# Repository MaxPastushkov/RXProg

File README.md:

RXProg uses an STM32 to emulate the drum machine's SRAM chips, allowing programming over USB

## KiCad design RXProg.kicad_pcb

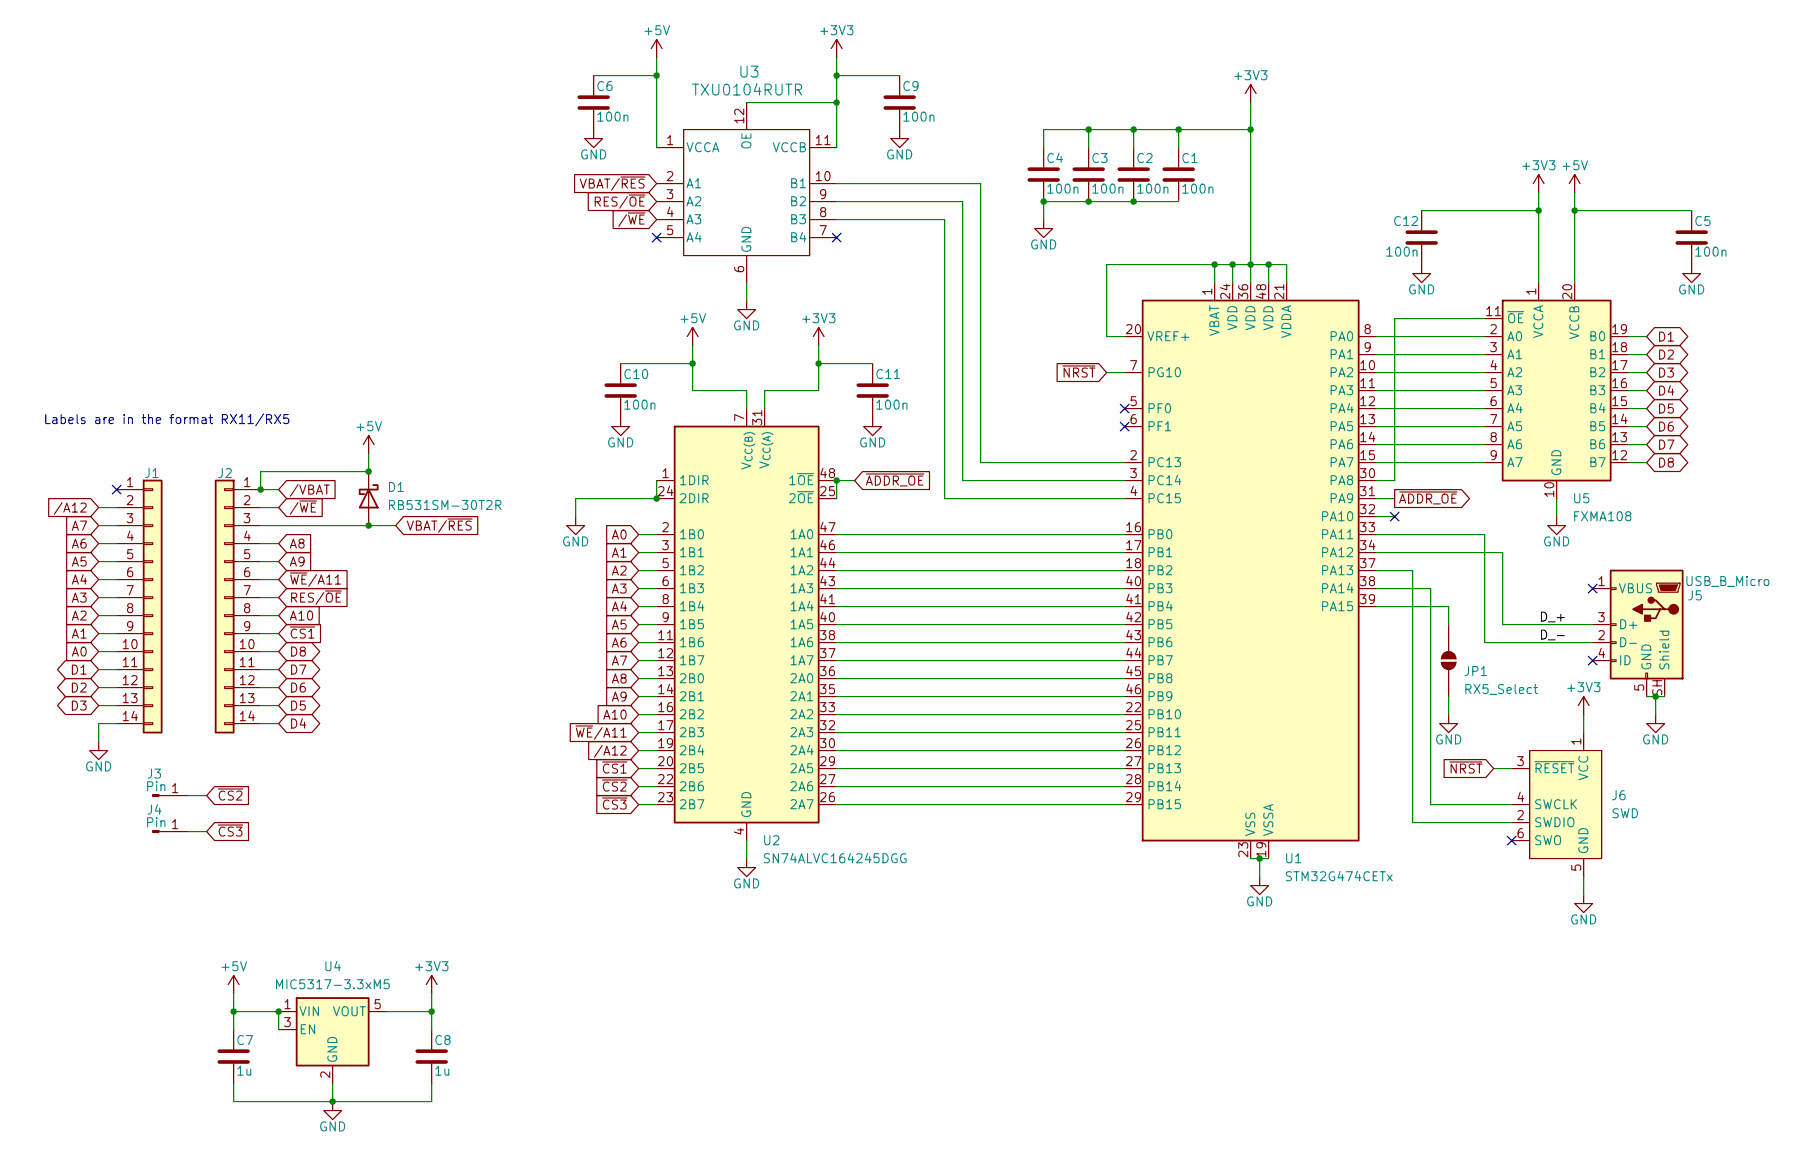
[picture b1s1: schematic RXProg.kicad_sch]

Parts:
C1, C2, C3, C4, C5, C6, C9, C10, C11, C12: 100n; C_0201_0603Metric
C7, C8: 1u; C_0201_0603Metric
D1: RB531SM-30T2R; D_SOD-523
J1, J2: Conn_01x14; PinHeader_1x14_P2.54mm_Vertical
J3, J4: Pin
J5: USB_B_Micro; USB_Micro-B_Amphenol_10103594-0001LF_Horizontal
J6: SWD; Tag-Connect_TC2030-IDC-NL_2x03_P1.27mm_Vertical
JP1: RX5_Select; SolderJumper-2_P1.3mm_Open_RoundedPad1.0x1.5mm
U1: STM32G474CETx; LQFP-48_7x7mm_P0.5mm
U2: SN74ALVC164245DGG; TSSOP-48_6.1x12.5mm_P0.5mm
U3: TXU0104RUTR; QFN_04RUTR_TEX
U4: MIC5317-3.3xM5; SOT-23-5
U5: FXMA108; WQFN-20-1EP_2.5x4.5mm_P0.5mm_EP1x2.9mm

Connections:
+3V3: C1.1, C2.1, C3.1, C4.1, C8.1, C9.1, C11.1, C12.1, J6.1 (VCC), U1.1 (VBAT), U1.20 (VREF+), U1.21 (VDDA), U1.24 (VDD), U1.36 (VDD), U1.48 (VDD), U2.31 (V_{CC(A)}), U2.42 (V_{CC(A)}), U3.11 (VCCB), U3.12 (OE), U4.5 (VOUT), U5.1 (VCCA)
/D_+: J5.3 (D+), U1.34 (PA12)
/D_-: J5.2 (D-), U1.33 (PA11)
A0: J1.10, U2.2 (1B0)
A1: J1.9, U2.3 (1B1)
A2: J1.8, U2.5 (1B2)
A3: J1.7, U2.6 (1B3)
A4: J1.6, U2.8 (1B4)
A5: J1.5, U2.9 (1B5)
A6: J1.4, U2.11 (1B6)
A7: J1.3, U2.12 (1B7)
A8: J2.4, U2.13 (2B0)
A9: J2.5, U2.14 (2B1)
A10: J2.8, U2.16 (2B2)
D1: J1.11, U5.19 (B0)
D2: J1.12, U5.18 (B1)
D3: J1.13, U5.17 (B2)
D4: J2.14, U5.16 (B3)
D5: J2.13, U5.15 (B4)
D6: J2.12, U5.14 (B5)
D7: J2.11, U5.13 (B6)
D8: J2.10, U5.12 (B7)
GND: C1.2, C2.2, C3.2, C4.2, C5.2, C6.2, C7.2, C8.2, C9.2, C10.2, C11.2, C12.2, J1.14, J5.5 (GND), J5.SH (Shield), J6.5 (GND), JP1.1 (A), U1.19 (VSSA), U1.23 (VSS), U1.35 (VSS), U1.47 (VSS), U2.1 (1DIR), U2.4 (GND), U2.10 (GND), U2.15 (GND), U2.21 (GND), U2.24 (2DIR), U2.28 (GND), U2.34 (GND), U2.39 (GND), U2.45 (GND), U3.6 (GND), U4.2 (GND), U5.10 (GND)
unnamed: J6.4 (SWCLK), U1.38 (PA14)
unnamed: J6.2 (SWDIO), U1.37 (PA13)
unnamed: JP1.2 (B), U1.39 (PA15)
unnamed: U1.8 (PA0), U5.2 (A0)
unnamed: U1.9 (PA1), U5.3 (A1)
unnamed: U1.10 (PA2), U5.4 (A2)
unnamed: U1.11 (PA3), U5.5 (A3)
unnamed: U1.12 (PA4), U5.6 (A4)
unnamed: U1.13 (PA5), U5.7 (A5)
unnamed: U1.14 (PA6), U5.8 (A6)
unnamed: U1.15 (PA7), U5.9 (A7)
unnamed: U1.30 (PA8), U5.11 (~OE)
unnamed: U1.16 (PB0), U2.47 (1A0)
unnamed: U1.17 (PB1), U2.46 (1A1)
unnamed: U1.18 (PB2), U2.44 (1A2)
unnamed: U1.40 (PB3), U2.43 (1A3)
unnamed: U1.41 (PB4), U2.41 (1A4)
unnamed: U1.42 (PB5), U2.40 (1A5)
unnamed: U1.43 (PB6), U2.38 (1A6)
unnamed: U1.44 (PB7), U2.37 (1A7)
unnamed: U1.45 (PB8), U2.36 (2A0)
unnamed: U1.46 (PB9), U2.35 (2A1)
unnamed: U1.22 (PB10), U2.33 (2A2)
unnamed: U1.25 (PB11), U2.32 (2A3)
unnamed: U1.26 (PB12), U2.30 (2A4)
unnamed: U1.27 (PB13), U2.29 (2A5)
unnamed: U1.28 (PB14), U2.27 (2A6)
unnamed: U1.29 (PB15), U2.26 (2A7)
unnamed: U1.2 (PC13), U3.10 (B1)
unnamed: U1.3 (PC14), U3.9 (B2)
unnamed: U1.4 (PC15), U3.8 (B3)
RES/~OE: J2.7, U3.3 (A2)
VBAT/~RES: D1.2 (A), J2.3, U3.2 (A1)
/A12: J1.2, U2.19 (2B4)
/VBAT: C5.1, C6.1, C7.1, C10.1, D1.1 (K), J2.1, U2.7 (V_{CC(B)}), U2.18 (V_{CC(B)}), U3.1 (VCCA), U4.1 (VIN), U4.3 (EN), U5.20 (VCCB)
/~WE: J2.2, U3.4 (A3)
~ADDR_OE: U1.31 (PA9), U2.25 (2~OE), U2.48 (1~OE)
~CS1: J2.9, U2.20 (2B5)
~CS2: J3.1 (Pin_1_1), U2.22 (2B6)
~CS3: J4.1 (Pin_1_1), U2.23 (2B7)
~NRST: J6.3 (~RESET), U1.7 (PG10)
~WE/A11: J2.6, U2.17 (2B3)

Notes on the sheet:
Labels are in the format RX11/RX5

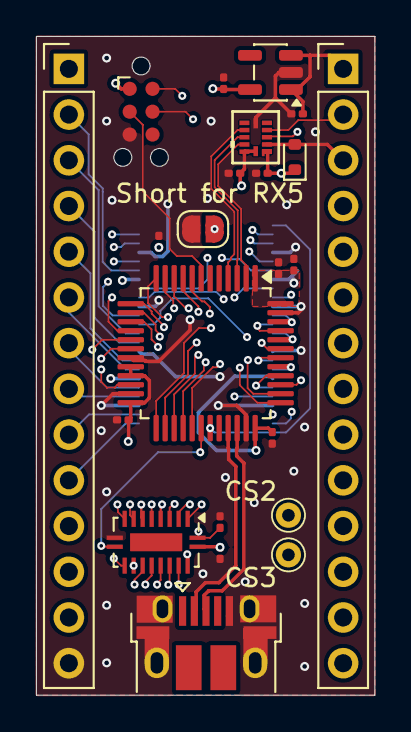
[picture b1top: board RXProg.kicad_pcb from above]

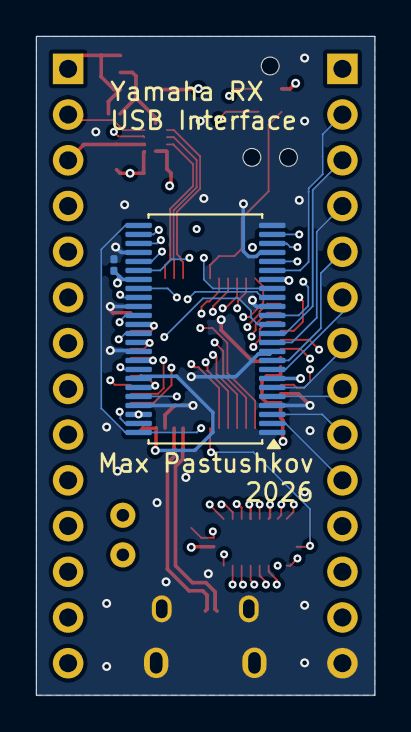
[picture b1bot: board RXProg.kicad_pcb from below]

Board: 6 copper layers, 18.8 x 36.6 mm, 25 parts (2 on the bottom side), 65 nets.

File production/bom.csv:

Designator,Footprint,Quantity,Value,LCSC Part #
"C1, C10, C11, C12, C2, C3, C4, C5, C6, C9",0201,10,100n,
"C7, C8",0201,2,1u,
D1,D_SOD-523,1,RB531SM-30T2R,
"J1, J2",PinHeader_1x14_P2.54mm_Vertical,2,Conn_01x14,
"J3, J4",Pin,2,Pin,
J5,USB_Micro-B_Amphenol_10103594-0001LF_Horizontal,1,USB_B_Micro,
U1,LQFP-48_7x7mm_P0.5mm,1,STM32G474CETx,
U2,TSSOP-48_6.1x12.5mm_P0.5mm,1,SN74ALVC164245DGG,
U3,QFN_04RUTR_TEX,1,TXU0104RUTR,
U4,SOT-23-5,1,MIC5317-3.3xM5,
U5,WQFN-20-1EP_2.5x4.5mm_P0.5mm_EP1x2.9mm,1,FXMA108,

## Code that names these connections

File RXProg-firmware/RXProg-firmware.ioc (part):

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Mcu.Name=STM32G474C(B-C-E)Tx
Mcu.Package=LQFP48
Mcu.UserName=STM32G474CETx
PA0.GPIOParameters=GPIO_Label
PA0.GPIO_Label=D0
PA0.Signal=GPIO_Output
PA1.GPIOParameters=GPIO_Label
PA1.GPIO_Label=D1
PA1.Signal=GPIO_Output
PA11.Mode=Device
PA11.Signal=USB_DM
PA12.Mode=Device
PA12.Signal=USB_DP
PA15.GPIOParameters=GPIO_PuPd,GPIO_Label
PA15.GPIO_Label=RX5
PA15.GPIO_PuPd=GPIO_PULLUP
PA15.Signal=GPIO_Input
PA2.GPIOParameters=GPIO_Label
PA2.GPIO_Label=D2
PA2.Signal=GPIO_Output
PA3.GPIOParameters=GPIO_Label
PA3.GPIO_Label=D3
PA3.Signal=GPIO_Output
PA4.GPIOParameters=GPIO_Label
PA4.GPIO_Label=D4
PA4.Signal=GPIO_Output
PA5.GPIOParameters=GPIO_Label
PA5.GPIO_Label=D5
PA5.Signal=GPIO_Output
PA6.GPIOParameters=GPIO_Label
PA6.GPIO_Label=D6
PA6.Signal=GPIO_Output
PA7.GPIOParameters=GPIO_Label
PA7.GPIO_Label=D7
PA7.Signal=GPIO_Output
PA8.GPIOParameters=GPIO_Label
PA8.GPIO_Label=DATA_OE
PA8.Signal=GPIO_Output
PA9.GPIOParameters=GPIO_Label
PA9.GPIO_Label=ADDR_OE
PA9.Signal=GPIO_Output
PB0.GPIOParameters=GPIO_Label
PB0.GPIO_Label=A0
PB0.Signal=GPIO_Input
PB1.GPIOParameters=GPIO_Label
PB1.GPIO_Label=A1
PB1.Signal=GPIO_Input
PB10.GPIOParameters=GPIO_Label
PB10.GPIO_Label=A10
PB10.Signal=GPIO_Input
PB11.GPIOParameters=GPIO_Label
PB11.GPIO_Label=WE/A11
PB11.Signal=GPIO_Input
PB12.GPIOParameters=GPIO_Label
PB12.GPIO_Label=A12
PB12.Signal=GPIO_Input
PB13.GPIOParameters=GPIO_Label,GPIO_ModeDefaultEXTI
PB13.GPIO_Label=CS1
PB13.GPIO_ModeDefaultEXTI=GPIO_MODE_IT_FALLING
PB13.Signal=GPXTI13
PB14.GPIOParameters=GPIO_Label,GPIO_ModeDefaultEXTI
PB14.GPIO_Label=CS2
PB14.GPIO_ModeDefaultEXTI=GPIO_MODE_IT_FALLING
PB14.Signal=GPXTI14
PB15.GPIOParameters=GPIO_Label,GPIO_ModeDefaultEXTI
PB15.GPIO_Label=CS3
PB15.GPIO_ModeDefaultEXTI=GPIO_MODE_IT_FALLING
PB15.Signal=GPXTI15
PB2.GPIOParameters=GPIO_Label
PB2.GPIO_Label=A2
PB2.Signal=GPIO_Input
PB3.GPIOParameters=GPIO_Label
PB3.GPIO_Label=A3
PB3.Signal=GPIO_Input
PB4.GPIOParameters=GPIO_Label
PB4.GPIO_Label=A4
PB4.Signal=GPIO_Input
PB5.GPIOParameters=GPIO_Label
PB5.GPIO_Label=A5
PB5.Signal=GPIO_Input
PB6.GPIOParameters=GPIO_Label
PB6.GPIO_Label=A6
PB6.Signal=GPIO_Input
PB7.GPIOParameters=GPIO_Label
PB7.GPIO_Label=A7
PB7.Signal=GPIO_Input
PB8-BOOT0.GPIOParameters=GPIO_Label
PB8-BOOT0.GPIO_Label=A8
PB8-BOOT0.Signal=GPIO_Input
PB9.GPIOParameters=GPIO_Label
PB9.GPIO_Label=A9
PB9.Signal=GPIO_Input
PC13.GPIOParameters=GPIO_Label
PC13.GPIO_Label=VBAT/RES
PC13.Signal=GPIO_Input
PC14-OSC32_IN.GPIOParameters=GPIO_Label
PC14-OSC32_IN.GPIO_Label=RES/OE
PC14-OSC32_IN.Signal=GPIO_Input
PC15-OSC32_OUT.GPIOParameters=GPIO_Label
PC15-OSC32_OUT.GPIO_Label=WE
PC15-OSC32_OUT.Signal=GPIO_Input
RCC.HSE_VALUE=8000000
RCC.SYSCLKFreq_VALUE=144000000
RCC.SYSCLKSource=RCC_SYSCLKSOURCE_PLLCLK
board=custom

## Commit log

2026-05-20 Init
2026-05-20 Add level shifters
2026-05-21 Add firmware
2026-05-21 Start routing
2026-05-21 Continue
2026-05-22 Finished routing
2026-05-27 Finish routing (again)
2026-05-28 Time to reroute! (again)
2026-05-28 Fix vias
2026-05-28 Add jumper text
2026-05-29 Firmware working (?)
2026-05-29 Fix USB clock
2026-06-02 Finished access counting
2026-06-02 Remove pycache
